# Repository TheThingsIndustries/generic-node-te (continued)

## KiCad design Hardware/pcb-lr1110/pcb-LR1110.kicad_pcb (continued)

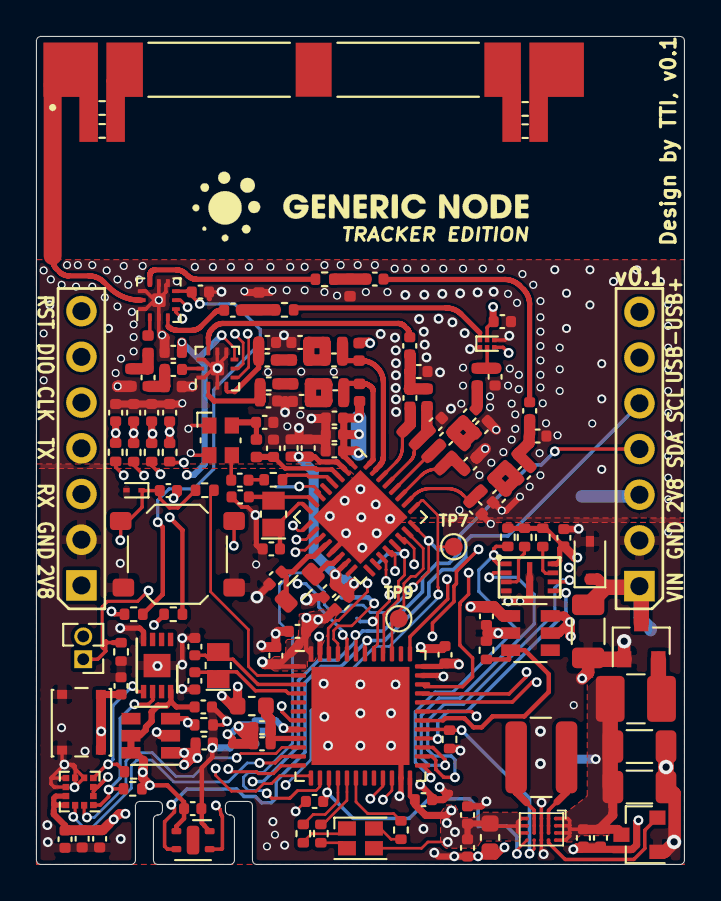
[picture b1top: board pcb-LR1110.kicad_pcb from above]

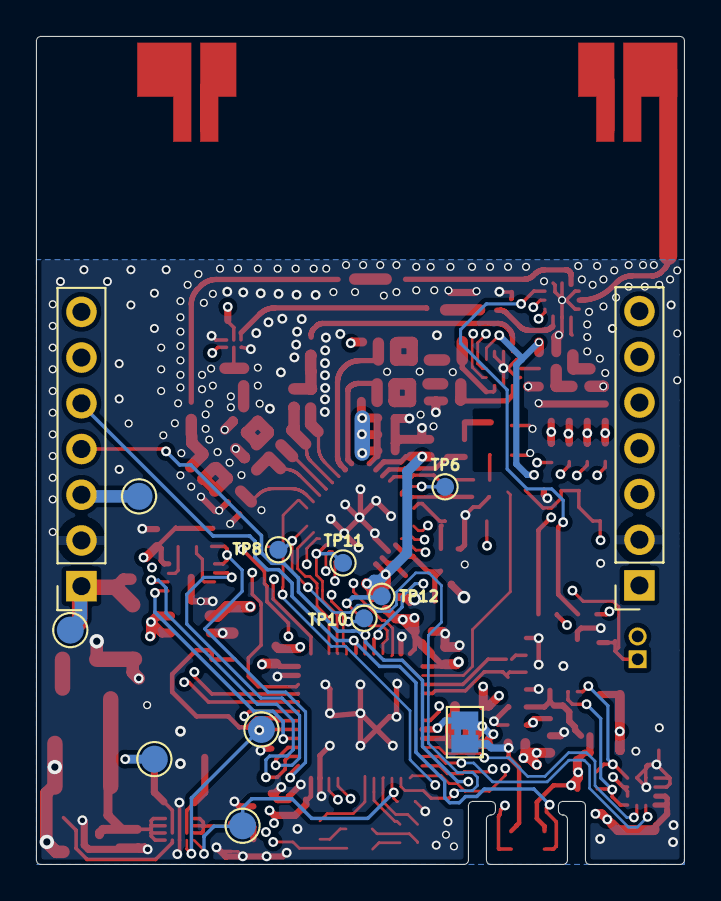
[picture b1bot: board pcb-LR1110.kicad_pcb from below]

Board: 4 copper layers, 36.0 x 46.0 mm, 161 parts (13 on the bottom side), 108 nets.

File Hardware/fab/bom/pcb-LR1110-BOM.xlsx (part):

Source: | C:\Users\orkha\OneDrive\TTI_Files\Generic_Node_TE\Hardware\pcb\pcb-LR1110.sch
Date: | 2/17/2021 2:02:27 PM
Tool: | Eeschema (5.1.8)-1
Generator: | C:\Program Files\KiCad\bin\scripting\plugins/bom_csv_grouped_by_value.py
Component Count: | 150
Individual Components:
Collated Components:
Item | Qty | Reference(s) | Value | MPN | ALT_MPN | LibPart | Footprint
1 | 1 | AE1 | NN03-310 | NN03-310 |  | lr1110-lib:NN03-310 | lr1110-lib:NN03-310_S
2 | 7 | C1, C8, C11, C12, C43, C69, C70 | 1uF | CL05A105KQ5NNNC |  | Device:C | Capacitor_SMD:C_0402_1005Metric
3 | 14 | C2, C7, C10, C32, C33, C36, C37, C38, C40, C42, C67, C68, C71, C72 | 100nF | CC0402KRX7R7BB104 |  | Device:C | Capacitor_SMD:C_0402_1005Metric
4 | 3 | C3, C4, C5 | 100uF | JMK316ABJ107ML-T |  | Device:C | Capacitor_SMD:C_1206_3216Metric
5 | 1 | C6 | 470pF | CL05C471JO5NNNC |  | Device:C_Small | Capacitor_SMD:C_0402_1005Metric
6 | 1 | C9 | 22uF | CC0603MRX5R5BB226 | JMK107BBJ226MA | Device:C | Capacitor_SMD:C_0603_1608Metric
7 | 2 | C13, C34 | 100nF | CC0402KRX7R7BB104 |  | Device:C_Small | Capacitor_SMD:C_0402_1005Metric
8 | 2 | C14, C48 | 1.2pF | GRM1555C1H1R2BA01D |  | Device:C_Small | Capacitor_SMD:C_0402_1005Metric
9 | 7 | C15, C17, C47, C57, C58, C65, C66 | 1nF | GRM155R71C102KA01D |  | Device:C_Small | Capacitor_SMD:C_0402_1005Metric
10 | 5 | C16, C27, C28, C41, C46 | 47pF | GRM1555C1H470JA01D |  | Device:C_Small | Capacitor_SMD:C_0402_1005Metric
11 | 2 | C18, C30 | 6.8pF | GRM1555C1H6R8CA01D |  | Device:C_Small | Capacitor_SMD:C_0402_1005Metric
12 | 1 | C20 | 10pF | C0402C100K5RAC7867 |  | Device:C_Small | Capacitor_SMD:C_0402_1005Metric
13 | 1 | C21 | 1.8pF | GRM1555C1H1R8BA01D |  | Device:C_Small | Capacitor_SMD:C_0402_1005Metric
14 | 4 | C22, C23, C73, C74 | 5.6pF | CC0402BRNPO9BN5R6 |  | Device:C_Small | Capacitor_SMD:C_0402_1005Metric
15 | 1 | C24 | 2pF | GJM1555C1H2R0WB01 |  | Device:C_Small | Capacitor_SMD:C_0402_1005Metric
16 | 2 | C25, C52 | 1.1pF | GJM1555C1H1R1WB01 |  | Device:C_Small | Capacitor_SMD:C_0402_1005Metric
17 | 1 | C26 | 2.2nF | GRM155R71H222KA01D |  | Device:C_Small | Capacitor_SMD:C_0402_1005Metric
18 | 1 | C29 | 3pF | GRM1555C1H3R0BA01J |  | Device:C_Small | Capacitor_SMD:C_0402_1005Metric
19 | 1 | C35 | 10uF | JMK107ABJ106KA-T | C1608X5R0J106K080AB | Device:C | Capacitor_SMD:C_0402_1005Metric
20 | 3 | C39, C45, C50 | 1.5pF | GRM1555C1H1R5BA01D |  | Device:C_Small | Capacitor_SMD:C_0402_1005Metric
21 | 2 | C44, C54 | 47pF | GRM1555C1H470JA01D |  | Device:C | Capacitor_SMD:C_0402_1005Metric
22 | 2 | C49, C60 | DNM | ~ |  | Device:C_Small | Capacitor_SMD:C_0402_1005Metric
23 | 1 | C51 | 12pF | GRM1555C1H120JA01D |  | Device:C_Small | Capacitor_SMD:C_0402_1005Metric
24 | 2 | C53, C56 | 0.5pF | GRM1555C1HR50BA01D |  | Device:C_Small | Capacitor_SMD:C_0402_1005Metric
25 | 1 | C55 | 1pF | GRM1555C1H1R0BA01D |  | Device:C_Small | Capacitor_SMD:C_0402_1005Metric
26 | 1 | C59 | 0.3pF | GJM1555C1HR30WB01 |  | Device:C_Small | Capacitor_SMD:C_0402_1005Metric
27 | 1 | C61 | 33pF | GRM1555C1H330JA01D |  | Device:C_Small | Capacitor_SMD:C_0402_1005Metric
28 | 1 | C62 | 1.3pF | GRM1555C1H1R3BA01D |  | Device:C_Small | Capacitor_SMD:C_0402_1005Metric
29 | 1 | C63 | 1.6pF | GRM1555C1H1R6BA01D |  | Device:C_Small | Capacitor_SMD:C_0402_1005Metric
30 | 1 | C64 | 0.7pF | GRM1555C1HR70BA01D |  | Device:C_Small | Capacitor_SMD:C_0402_1005Metric
31 | 1 | D1 | PESD5V0S1BA | PESD5V0S1BA,115 |  | Device:D_TVS_ALT | Diode_SMD:D_SOD-323
32 | 1 | D2 | FM-B2020RGBA | FM-B2020RGBA-HG |  | pcb-LR1110-rescue:FM-B2020RGBA-node-lib-v1-pcb-LR1110-rescue | LED_SMD:LED_Cree-PLCC4_2x2mm_CW
33 | 1 | D4 | ESD9D5V | Diode_SMD:D_SOD-923 |  | Device:D_Zener | Diode_SMD:D_SOD-923
34 | 1 | F1 | PTC 13V 1A | SMD1210-050 |  | Device:Polyfuse | Fuse:Fuse_1210_3225Metric_Castellated
35 | 1 | FB1 | 600R @100MHz | BLM18AG601SN1D |  | Device:Ferrite_Bead_Small | Inductor_SMD:L_0603_1608Metric
36 | 1 | J2 | BOOT0 | DNM |  | Connector_Generic:Conn_01x02 | Connector_PinHeader_1.27mm:PinHeader_1x02_P1.27mm_Vertical
37 | 1 | J8 | DEBUG | DNM | C124418 | Connector_Generic:Conn_01x07 | Connector_PinSocket_2.54mm:PinSocket_1x07_P2.54mm_Vertical
38 | 1 | J9 | USB/I2C | DNM | C124418 | Connector_Generic:Conn_01x07 | Connector_PinSocket_2.54mm:PinSocket_1x07_P2.54mm_Vertical
39 | 1 | JP3 | NetTie | DNM |  | Device:Jumper_NC_Small | Jumper:SolderJumper-2_P1.3mm_Bridged2Bar_Pad1.0x1.5mm
40 | 1 | L1 | 2.2uH | HPC4012TF-2R2M |  | Device:L_Core_Ferrite | node-lib-v1:L_HPC4012TF-2R2M
41 | 1 | L2 | 10R @100MHz | BLM15HG102SN1D |  | Device:L_Small | Inductor_SMD:L_0402_1005Metric
42 | 1 | L3 | 3.3nH | LQW15AN3N3C80D |  | Device:L_Small | Inductor_SMD:L_0402_1005Metric
43 | 1 | L4 | 8.2nH | LQW15AN8N2J00D |  | Device:L_Small | Inductor_SMD:L_0402_1005Metric
44 | 3 | L5, L7, L12 | 47nH | LQW15AN47NJ00D |  | Device:L_Small | Inductor_SMD:L_0402_1005Metric
45 | 1 | L6 | 5.9nH | LQW15AN5N9G80 |  | Device:L_Small | Inductor_SMD:L_0402_1005Metric
46 | 3 | L8, L13, L14 | 9.5nH | LQW18AN9N5G80 |  | Device:L_Small | Inductor_SMD:L_0402_1005Metric
47 | 1 | L9 | 2.7nH | LQW15AN2N7C00D |  | Device:L_Small | Inductor_SMD:L_0402_1005Metric
48 | 1 | L10 | 6.8nH | LQW15AN6N8J00D |  | Device:L_Small | Inductor_SMD:L_0402_1005Metric
49 | 1 | L11 | 22nH | LQW15AN22NH00D |  | Device:L_Small | Inductor_SMD:L_0402_1005Metric
50 | 1 | L15 | DNM | DNM |  | Device:L_Small | Inductor_SMD:L_0402_1005Metric
51 | 1 | L16 | 33nH | LQW15AN33NJ00D |  | Device:L_Small | Inductor_SMD:L_0402_1005Metric
52 | 1 | L17 | 7.9nH | LQW15AN7N9G80 |  | Device:L_Small | Inductor_SMD:L_0402_1005Metric
53 | 2 | L18, L19 | 3.6nH | LQW15AN3N6C10D |  | Device:L_Small | Inductor_SMD:L_0402_1005Metric
54 | 1 | L20 | 5.6nH | LQW15AN5N6G80 |  | Device:L_Small | Inductor_SMD:L_0402_1005Metric
55 | 1 | L21 | 15uH | MLZ2012M150W |  | Device:L | Inductor_SMD:L_0805_2012Metric
56 | 1 | N1 | BoLink-16174435 | DNM | BL 704020 WL2-9005 | Mechanical:Housing | lr1110-lib:BoLink_704025
57 | 1 | Q1 | CEN2321A | CEN2321A |  | Device:Q_PMOS_GSD | Package_TO_SOT_SMD:SOT-23
58 | 1 | R1 | 220R | RC0402FR-07220RL |  | Device:R_US | Resistor_SMD:R_0402_1005Metric
59 | 3 | R2, R3, R4 | 100K | RC0402FR-07100KL |  | Device:R | Resistor_SMD:R_0402_1005Metric
60 | 11 | R5, R17, R18, R19, R20, R21, R24, R25, R26, R27, R28 | 0R |  |  | Device:R_US | Resistor_SMD:R_0402_1005Metric
61 | 1 | R6 | 1K | RC0402FR-071KL |  | Device:R | Resistor_SMD:R_0402_1005Metric
62 | 2 | R7, R8 | 330R | AC0402FR-07330RL |  | Device:R | Resistor_SMD:R_0402_1005Metric
63 | 2 | R10, R11 | DNM | DNM |  | Device:R | Resistor_SMD:R_0402_1005Metric
64 | 1 | R12 | 10K | AC0402JR-0710KL |  | Device:R | Resistor_SMD:R_0402_1005Metric
65 | 1 | R13 | 100R | RC0402FR-07100RL |  | Device:R | Resistor_SMD:R_0402_1005Metric
66 | 2 | R15, R16 | 4K7 | AC0402FR-074K7L |  | Device:R | Resistor_SMD:R_0402_1005Metric
67 | 2 | R22, R23 | DNM |  |  | Device:R_US | Resistor_SMD:R_0402_1005Metric
68 | 1 | R29 | 10K |  |  | Device:R_US | Resistor_SMD:R_0402_1005Metric
69 | 1 | SW1 | USR_BTN | KSC721GLFS |  | Switch:SW_Push | node-lib-v1:PushButton_UK-B0234-SP25Y
70 | 1 | SW2 | SW_Push |  |  | Switch:SW_Push | node-lib-v1:SW_SPST_SKSHABE010
71 | 1 | U1 | RP605Z283B | RP605Z283B-E2-F |  | pcb-LR1110-rescue:RP605Zx-node-lib-v1-pcb-LR1110-rescue | node-lib-v1:WLCSP-20-P3_1.994x1.609mm_Layout5x4_P0.4mm
72 | 1 | U2 | TPS3839G25 | TPS3839G25DBZ |  | Power_Supervisor:TPS3839DBZ | Package_TO_SOT_SMD:SOT-23
73 | 2 | U3, U4 | TPS22917DBV | TPS22917DBVR |  | Power_Management:TPS22917DBV | Package_TO_SOT_SMD:SOT-23-6
74 | 2 | U5, U6 | SKY13588-460LF | SKY13588-460LF |  | lr1110-lib:SKY13588-460LF | lr1110-lib:sQFN-12-1EP_2x2mm_P0.5mm_EP0.76x0.76mm
75 | 1 | U7 | BGA524N6 | BGA524N6 |  | lr1110-lib:BGA524N6 | lr1110-lib:TSNP-6-2-8
76 | 1 | U8 | STM32L073CZU6 | STM32L073CZU6 |  | lr1110-lib:STM32L073CZUx | Package_DFN_QFN:QFN-48-1EP_7x7mm_P0.5mm_EP5.45x5.45mm
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
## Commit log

2021-05-04 dev: Add github templates and ignores
2021-05-04 sch: Add schematics pdf file of STM32L0 and LR1110
2021-05-07 hw: Add KiCAD project files and production assets
2021-05-09 sw: Add basic FW and applications
2021-05-09 dev: Add environment gitignore
2021-05-09 doc: Add device renders and update readme on applications and SW setup
2021-06-11 doc: Update readme with key derivation notes
2021-06-11 app: Adjust join server and keys default configurations
2021-08-24 doc: Add generic-node License
